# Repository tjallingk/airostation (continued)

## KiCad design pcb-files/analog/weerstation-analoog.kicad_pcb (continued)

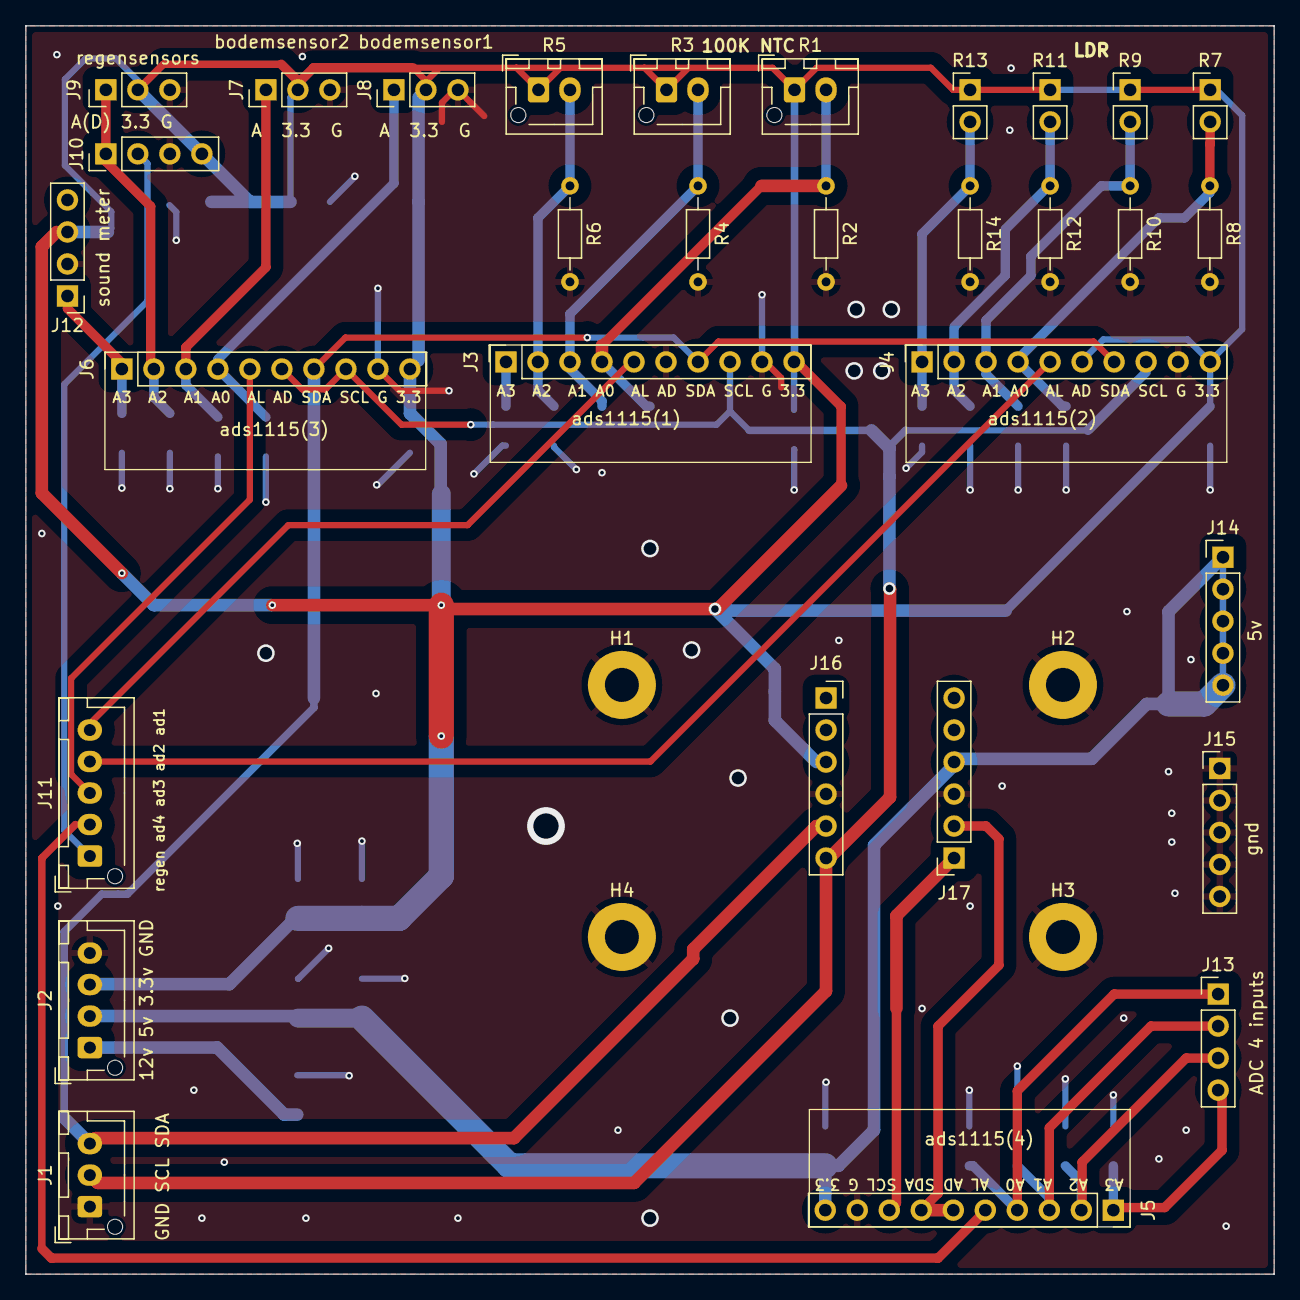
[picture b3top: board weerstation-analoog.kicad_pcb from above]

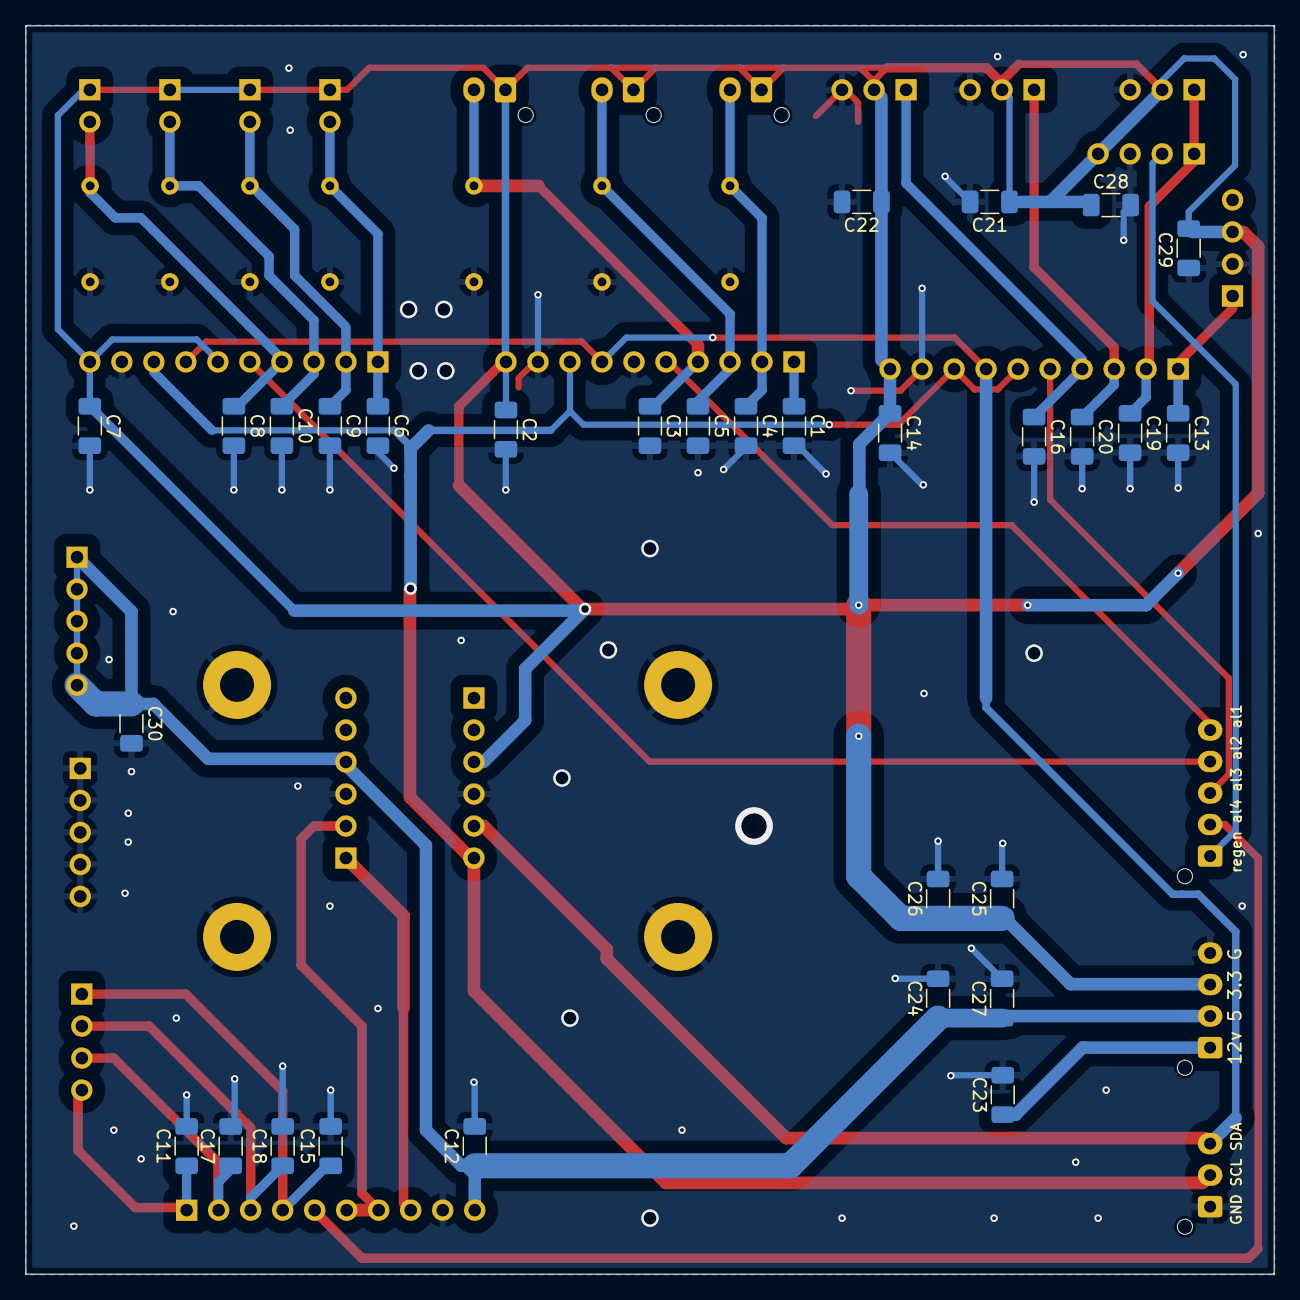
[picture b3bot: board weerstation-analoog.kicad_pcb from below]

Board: 2 copper layers, 99.1 x 99.1 mm, 65 parts (30 on the bottom side), 29 nets.

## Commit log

2024-11-16 license creative commens non comercial.
    i do like to have feedback and improvements etc but don't make money of of my project without my permission(im not saying its always a no money but not without my knowledge).
2024-11-16 v1 pcbs
    3 pcbs with images looking for feedback to get v2 better
2024-11-18 update pcb files better layout and grounding inproved
2024-11-19 pcbs as orderd. loads of grounding fixes
2025-01-11 first code
2025-08-27 code update trying mqtt auto discovery.
    added rain meter code cleanup mqtt topics in 1 file add ota and some more sensor stuff
2025-08-28 working auto discovery bug weird readings am2315 and aht21
    some bugs with reading weird temps and the 2 0x38 adress sensors also possible issue ota updates? but since upping buffer for mqtt the auto discovery topic stuff works great
